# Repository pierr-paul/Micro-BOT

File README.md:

# Micro'BOT

<p align="justify">
<strong>Micro'BOT est un robot éducatif open-source, conçu pour l'enseignement et l'expérimentation des concepts algorithmiques dans le cadre du programme de Numérique et Sciences Informatiques (NSI).</strong>
</p>

<br>

<br>

### Contexte du projet

<p align="justify">
Ce robot a été entièrement conçu et fabriqué dans le cadre d'un mémoire de Master MEEF NSI intitulé <strong>« Robots éducatifs et concepts algorithmiques : vers une meilleure motivation et une compréhension renforcée chez les élèves »</strong>.
</p>

<p align="justify">
L'objectif de ce travail de recherche est d'étudier l'impact de l'interaction avec un robot sur la motivation des élèves à apprendre les concepts algorithmiques. En s'appuyant sur les principes du <strong>constructivisme</strong> (Seymour Papert), le Micro'BOT a été pensé comme un médiateur tangible entre la théorie et la pratique. Il permet de matérialiser des abstractions logiques (boucles, conditions, séquençage) en actions physiques observables, transformant l'apprentissage en une expérience concrète et motivante.
</p>

<p align="justify">
La création d'un robot « sur mesure » plutôt que l'utilisation d'une solution commerciale répond à un double enjeu :
</p>

1.  **maîtriser l'outil expérimental** pour les besoins de la recherche.
2.  **garantir la reproductibilité de la recherche** en proposant une solution entièrement open-source et à faible coût.

### Description technique

Le Micro'BOT est une plateforme simple et modulaire :
-   le « cerveau » du robot est une carte **micro:bit** ;
-   le châssis, les fixations et les roues sont imprimés en 3D ;
-   une carte électronique s'interface avec la carte micro:bit pour piloter les moteurs et les capteurs.

### Programmation

Le robot peut être programmé avec **Microsoft MakeCode** : [https://makecode.microbit.org](https://makecode.microbit.org)

### Contenu du dépôt

Ce dépôt contient l'ensemble des fichiers nécessaires à la fabrication du Micro'BOT :

*   **`README.md`** : ce fichier de présentation.
*   **`LICENSE`** : la licence MIT du projet.
*   **`carte.sch`, `carte.brd`** : les fichiers de conception de la carte électronique (schéma et circuit imprimé) pour le logiciel Autodesk Eagle.
*   **`fixation r....stl` (plusieurs fichiers)** : les fichiers STL pour l'impression 3D des différentes pièces du châssis.
*   **`jante.stl`, `roulette....stl`** : les fichiers STL pour l'impression 3D des roues.
*   **`JLCPCB.zip`** : l'archive contenant les fichiers Gerber pour une commande professionnelle du circuit imprimé (PCB).
*   **`pxt.json`, `extension.ts`** : les fichiers de configuration pour l'extension Microsoft MakeCode.
*   **`actifs`, `classeur.xlsx`, `aide.txt`, `photo.png`, `.gitignore`** : les fichiers de configuration et ressources du projet.

### Licence
<p align="justify">
Ce projet est distribué sous la <strong>licence MIT</strong>. Vous êtes libre de l'utiliser, de le modifier et de le partager.
</p>

### Auteur
*   **M. Pierre PAUL**, dans le cadre du Master MEEF NSI (2024-2026) à l'INSPÉ de Lorraine - Université de Lorraine.
*   Sous la direction de **MM. David LANGLOIS et Alexis SCHEUER**.

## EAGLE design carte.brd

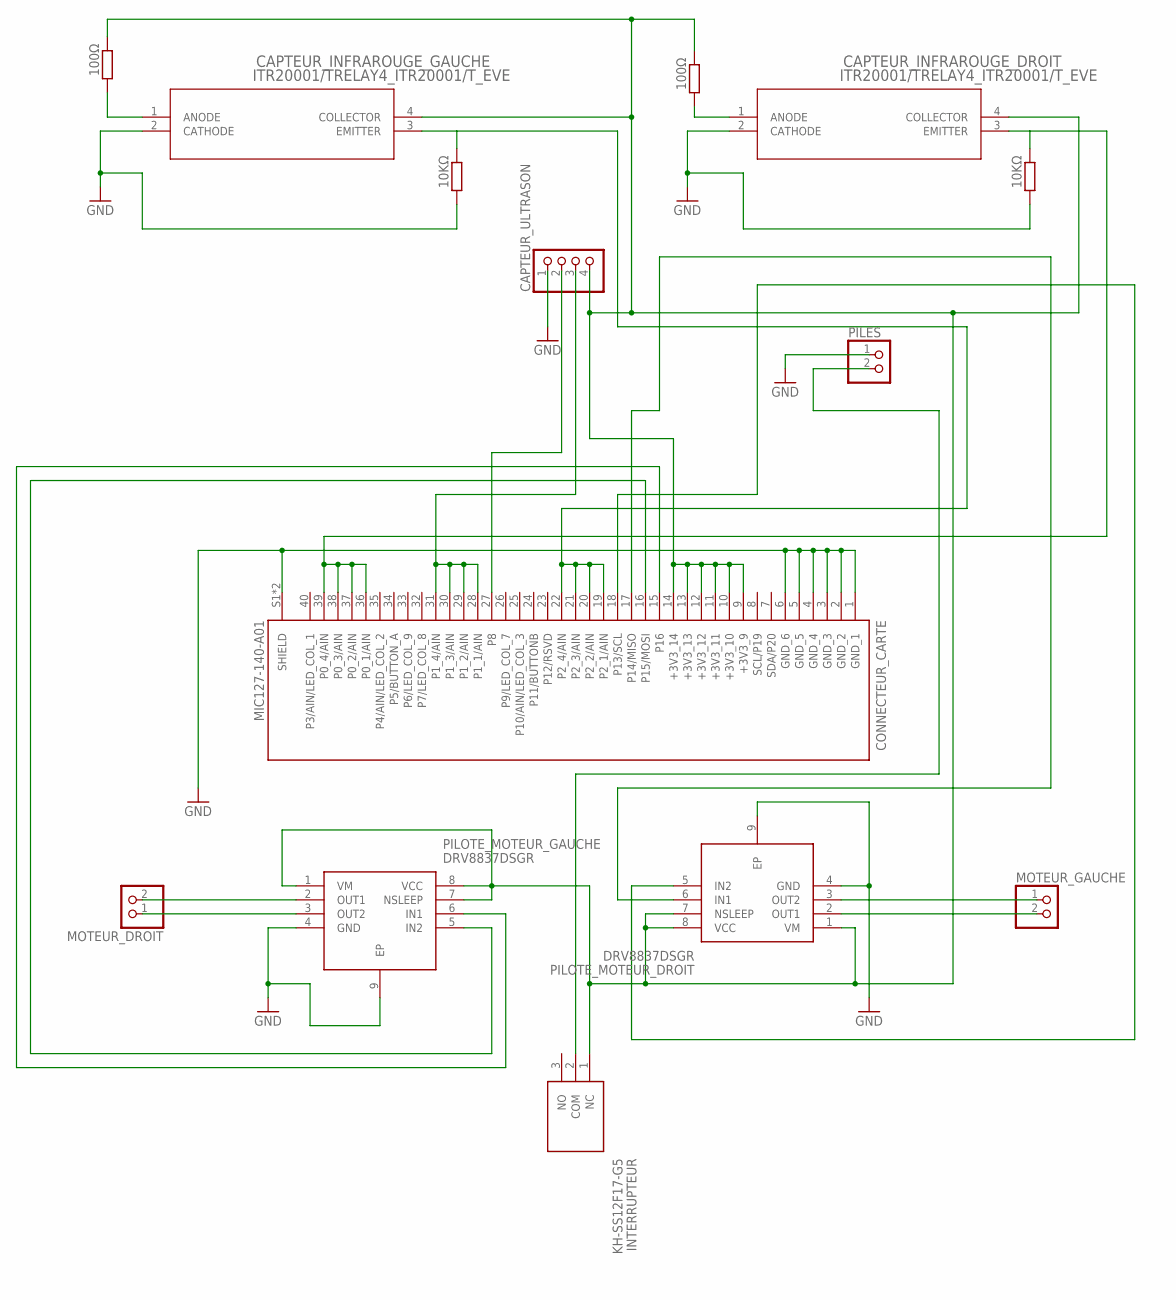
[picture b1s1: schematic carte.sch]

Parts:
CAPTEUR_INFRAROUGE_DROIT: ITR20001/TRELAY4_ITR20001/T_EVE; RELAY4_ITR20001/T_EVE; LCSC C264269
CAPTEUR_INFRAROUGE_GAUCHE: ITR20001/TRELAY4_ITR20001/T_EVE; RELAY4_ITR20001/T_EVE; LCSC C264269
CAPTEUR_ULTRASON: PINHD-1X4; 1X04
CONNECTEUR_CARTE: MIC127-140-A01; DONGGUAN_MIC127-140-A01; LCSC C5154027
INTERRUPTEUR: KH-SS12F17-G5; KHSS12F17G5; LCSC C5274464
MOTEUR_DROIT: PINHD-1X2; 1X02
MOTEUR_GAUCHE: PINHD-1X2; 1X02
PILES: PINHD-1X2; 1X02
PILOTE_MOTEUR_DROIT: DRV8837DSGR; SON50P200X200X80-9N; LCSC C39159
PILOTE_MOTEUR_GAUCHE: DRV8837DSGR; SON50P200X200X80-9N; LCSC C39159
R1, R3: 10KΩ; R0603; LCSC C25804
R2, R5: 100Ω; R0603; LCSC C22775

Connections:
3V: CAPTEUR_INFRAROUGE_DROIT.4 (COLLECTOR), CAPTEUR_INFRAROUGE_GAUCHE.4 (COLLECTOR), CAPTEUR_ULTRASON.4, CONNECTEUR_CARTE.9 (+3V3_9), CONNECTEUR_CARTE.10 (+3V3_10), CONNECTEUR_CARTE.11 (+3V3_11), CONNECTEUR_CARTE.12 (+3V3_12), CONNECTEUR_CARTE.13 (+3V3_13), CONNECTEUR_CARTE.14 (+3V3_14), INTERRUPTEUR.1 (NC), PILOTE_MOTEUR_DROIT.1 (VM), PILOTE_MOTEUR_DROIT.7 (NSLEEP), PILOTE_MOTEUR_DROIT.8 (VCC), PILOTE_MOTEUR_GAUCHE.1 (VM), PILOTE_MOTEUR_GAUCHE.7 (NSLEEP), PILOTE_MOTEUR_GAUCHE.8 (VCC), R2.1, R5.1
GND: CAPTEUR_INFRAROUGE_DROIT.2 (CATHODE), CAPTEUR_INFRAROUGE_GAUCHE.2 (CATHODE), CAPTEUR_ULTRASON.1, CONNECTEUR_CARTE.1 (GND_1), CONNECTEUR_CARTE.2 (GND_2), CONNECTEUR_CARTE.3 (GND_3), CONNECTEUR_CARTE.4 (GND_4), CONNECTEUR_CARTE.5 (GND_5), CONNECTEUR_CARTE.6 (GND_6), CONNECTEUR_CARTE.S1 (SHIELD), CONNECTEUR_CARTE.S2 (SHIELD), PILES.1, PILOTE_MOTEUR_DROIT.4 (GND), PILOTE_MOTEUR_DROIT.9 (EP), PILOTE_MOTEUR_GAUCHE.4 (GND), PILOTE_MOTEUR_GAUCHE.9 (EP), R1.2, R3.2
unnamed: MOTEUR_DROIT.2, PILOTE_MOTEUR_GAUCHE.2 (OUT1)
unnamed: MOTEUR_DROIT.1, PILOTE_MOTEUR_GAUCHE.3 (OUT2)
unnamed: MOTEUR_GAUCHE.1, PILOTE_MOTEUR_DROIT.3 (OUT2)
unnamed: MOTEUR_GAUCHE.2, PILOTE_MOTEUR_DROIT.2 (OUT1)
unnamed: CAPTEUR_INFRAROUGE_GAUCHE.1 (ANODE), R5.2
unnamed: INTERRUPTEUR.2 (COM), PILES.2
unnamed: CAPTEUR_INFRAROUGE_DROIT.1 (ANODE), R2.2
P0: CAPTEUR_INFRAROUGE_DROIT.3 (EMITTER), CONNECTEUR_CARTE.36 (P0_1/AIN), CONNECTEUR_CARTE.37 (P0_2/AIN), CONNECTEUR_CARTE.38 (P0_3/AIN), CONNECTEUR_CARTE.39 (P0_4/AIN), R3.1
P1: CAPTEUR_ULTRASON.3, CONNECTEUR_CARTE.28 (P1_1/AIN), CONNECTEUR_CARTE.29 (P1_2/AIN), CONNECTEUR_CARTE.30 (P1_3/AIN), CONNECTEUR_CARTE.31 (P1_4/AIN)
P2: CAPTEUR_INFRAROUGE_GAUCHE.3 (EMITTER), CONNECTEUR_CARTE.19 (P2_1/AIN), CONNECTEUR_CARTE.20 (P2_2/AIN), CONNECTEUR_CARTE.21 (P2_3/AIN), CONNECTEUR_CARTE.22 (P2_4/AIN), R1.1
P8: CAPTEUR_ULTRASON.2, CONNECTEUR_CARTE.27 (P8)
P13: CONNECTEUR_CARTE.18 (P13/SCL), PILOTE_MOTEUR_DROIT.5 (IN2)
P14: CONNECTEUR_CARTE.17 (P14/MISO), PILOTE_MOTEUR_DROIT.6 (IN1)
P15: CONNECTEUR_CARTE.16 (P15/MOSI), PILOTE_MOTEUR_GAUCHE.5 (IN2)
P16: CONNECTEUR_CARTE.15 (P16), PILOTE_MOTEUR_GAUCHE.6 (IN1)

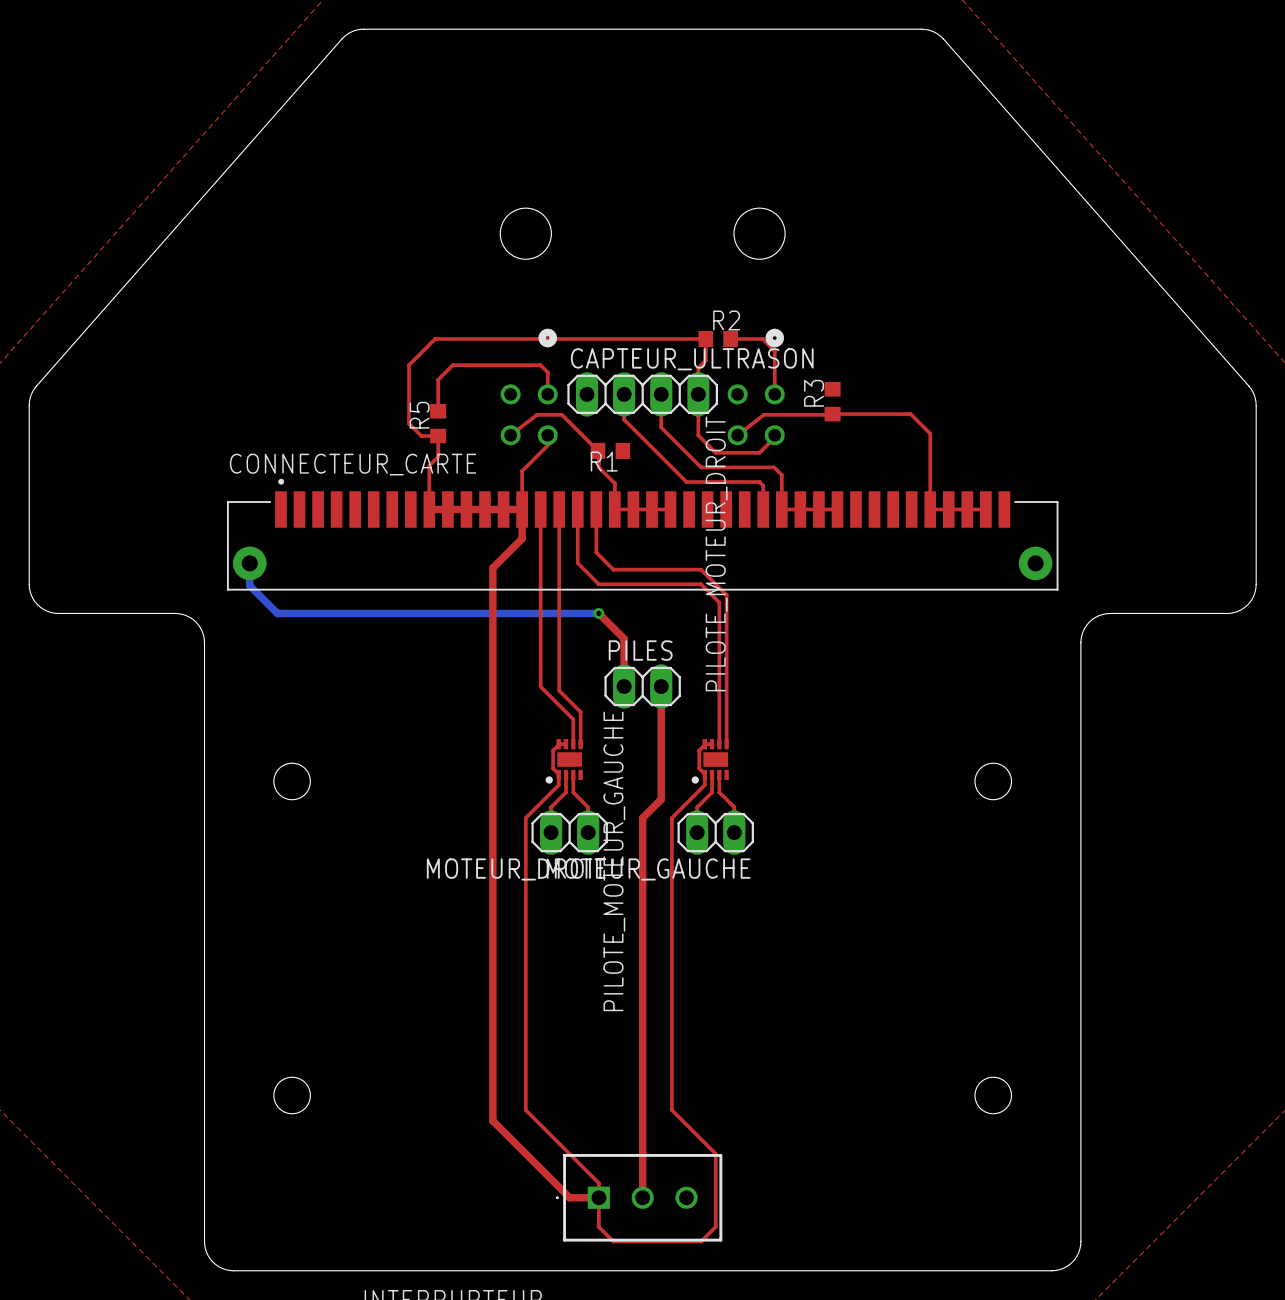
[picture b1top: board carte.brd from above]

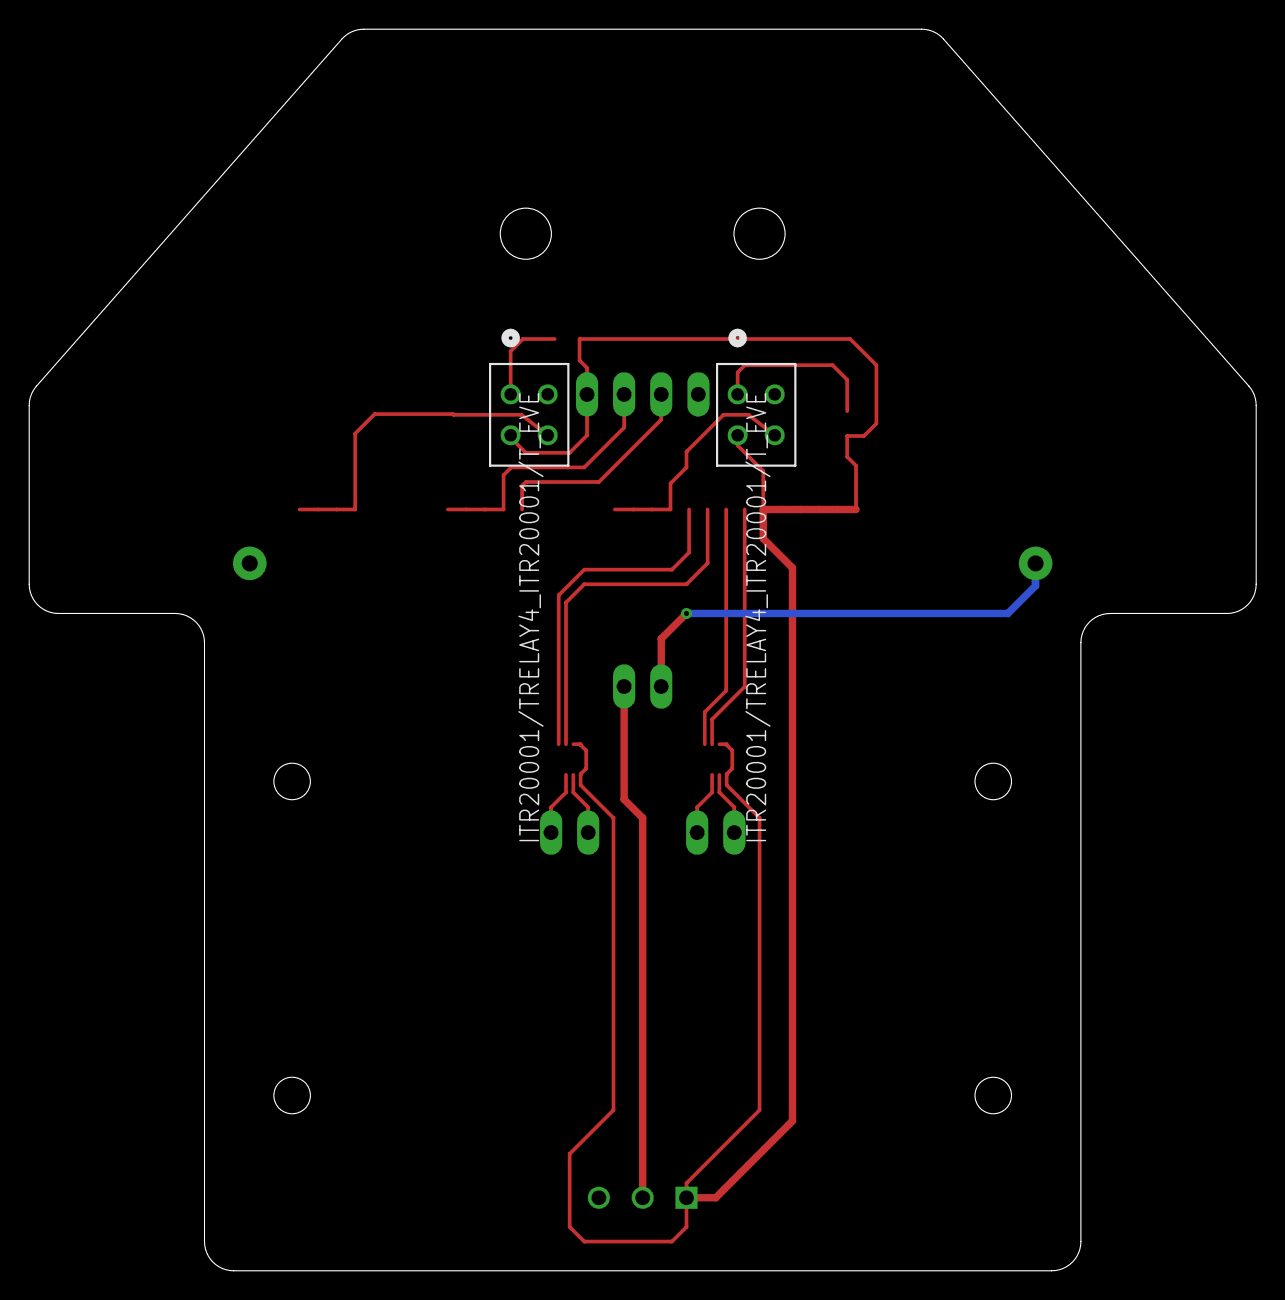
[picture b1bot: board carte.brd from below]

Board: 2 copper layers, 84.0 x 85.0 mm, 14 parts (2 on the bottom side), 17 nets.

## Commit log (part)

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2025-07-24 création du répertoire GIT
2025-07-24 mise à jour du fichier README
2025-07-24 régulation du contenu du répertoire GIT
2025-12-18 mise à jour du fichier extension
